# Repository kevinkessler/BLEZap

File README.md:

Schematic and Board for Bluetooth modification to the Zap recpetacle

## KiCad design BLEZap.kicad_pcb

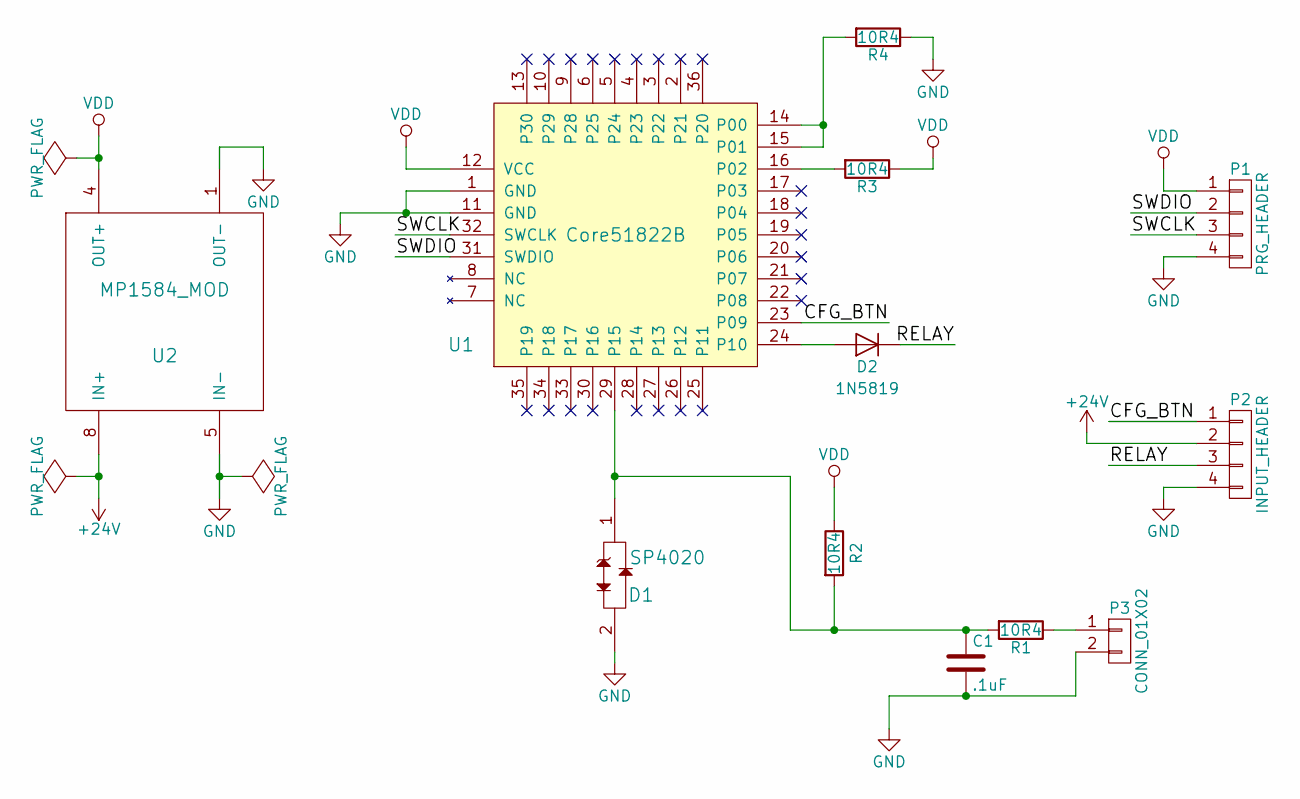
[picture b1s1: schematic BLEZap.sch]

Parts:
C1: .1uF; C_0805
D1: SP4020; SOD-323
D2: 1N5819; D_0805
P1: PRG_HEADER; Pin_Header_Straight_1x04
P2: INPUT_HEADER; Pin_Header_Straight_1x04
P3: CONN_01X02; Pin_Header_Angled_1x02
R1, R2, R3, R4: 10R4; R_0805
U1: Core51822B; CORE51822B
U2: MP1584_MOD; MP1584_MOD_ALL_UNDER

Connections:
+24V: P2.2, U2.8 (IN+)
/CFG_BTN: P2.1, U1.23 (P09)
/RELAY: D2.1 (K), P2.3
/SWCLK: P1.3, U1.32 (SWCLK)
/SWDIO: P1.2, U1.31 (SWDIO)
GND: C1.2, D1.2, P1.4, P2.4, P3.2, R4.1, U1.1 (GND), U1.11 (GND), U2.1 (OUT-), U2.5 (IN-)
unnamed: C1.1, D1.1, R1.2, R2.2, U1.29 (P15)
unnamed: D2.2 (A), U1.24 (P10)
unnamed: P3.1, R1.1
unnamed: R3.2, U1.16 (P02)
unnamed: R4.2, U1.14 (P00), U1.15 (P01)
VDD: P1.1, R2.1, R3.1, U1.12 (VCC), U2.4 (OUT+)

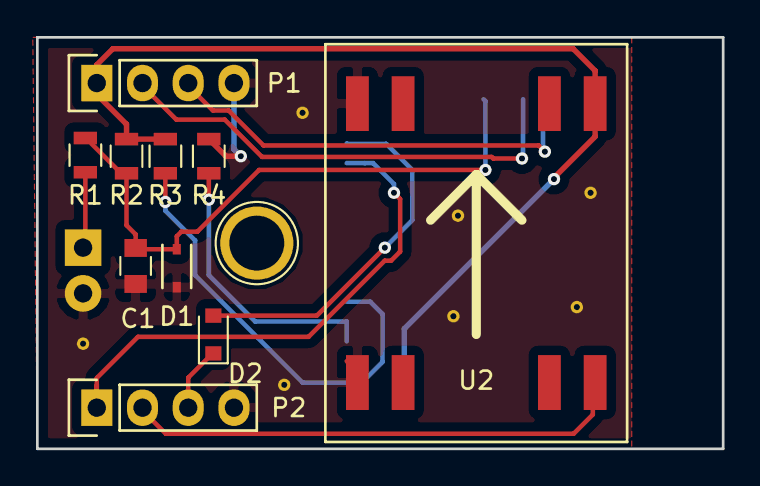
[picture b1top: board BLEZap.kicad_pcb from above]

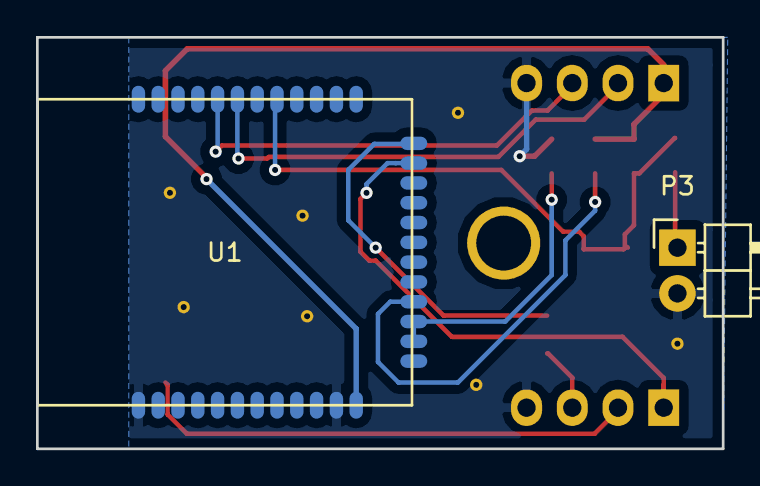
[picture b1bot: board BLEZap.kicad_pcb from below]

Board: 2 copper layers, 38.1 x 22.9 mm, 12 parts (2 on the bottom side), 12 nets.

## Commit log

2016-12-30 SP4020 Fix
2017-01-02 PCB Attempt
2017-01-03 PCB Ready
2017-01-04 SWD Swap
2017-01-04 Clean up
2017-01-26 Core51822 Fix
2017-01-28 Get Rid of _saved_
2017-01-28 Remove bak files
2017-01-31 Protection Diode
2017-02-02 Version 2
2017-03-20 Fix MP1584
2017-03-31 LP Filter
2017-03-31 Fix Labels
